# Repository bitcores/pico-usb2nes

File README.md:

# pico-usb2nes
RP2040 driven USB to controller interface for NES

This is based on the pico-usb2famikb project, using the same library for communicating with the NES/FC, but is focused on connecting to the controller port.

The only mode supported by default is the USB Keyboard Mouse Host mode (see [https://forums.nesdev.org/viewtopic.php?p=202489](https://forums.nesdev.org/viewtopic.php?p=202489) )

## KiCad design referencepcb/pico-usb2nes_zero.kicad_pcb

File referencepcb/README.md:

# pico-usb2nes Reference PCB
This directory contains reference a PCB design for the pico-usb2nes. It has not been designed by a experienced engineer, but it DOES work.

If you have some experience designing circuits like this, I would very much welcome improved designs.

For the reference design you will need:
* 1x Waveshare compatible RP2040-Zero
* 1x diode (I am using a 1N5819, 1N5817 better)
* 1x USB A type female port
* 2x 22ohm resistors
* 1x 100uf 16v capacitor (input from console)
* 1x four-channel logic level converter
* 1x NES controller port (PCB mountable)
* 5x pin headers (optional for i2c)

[This Youtube video](https://www.youtube.com/watch?v=ve_WcSxNZzQ) goes over the components and assembly.

These NES controller ports can be kinda hard to find, I will include a link to one source below (now unlisted, I am looking for other sources)

[https://aliexpress.com/item/1005009418780409.html](https://aliexpress.com/item/1005009418780409.html)

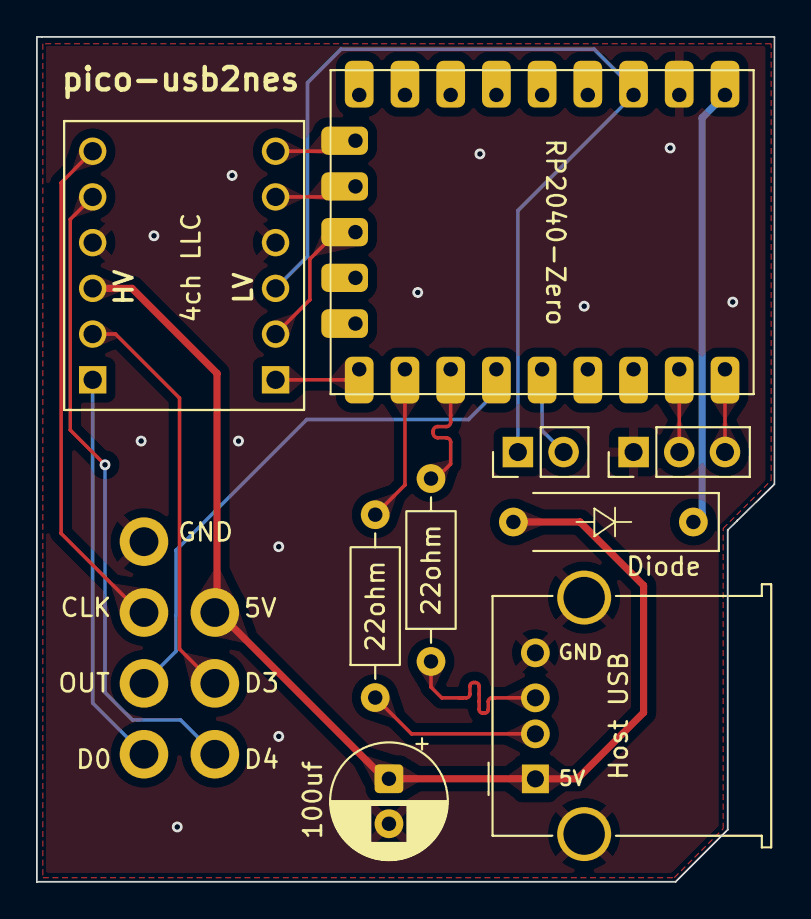
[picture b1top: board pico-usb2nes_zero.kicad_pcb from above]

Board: 2 copper layers, 41.0 x 46.9 mm, 8 parts (0 on the bottom side), 9 nets.

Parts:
4ch LLC: CONV_BOB-12009
22ohm, 22ohm#2: R_Axial_DIN0207_L6.3mm_D2.5mm_P10.16mm_Horizontal
100uf: CP_Radial_D6.3mm_P2.50mm
Diode: D_MELF-RM10_Universal_Handsoldering
Host USB: USB_A_Molex_67643_Horizontal
NES Controller Port: NES controller port
i2cENABLE: PinHeader_1x02_P2.54mm_Vertical

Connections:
5V: 4ch LLC.HV, 100uf.1, Diode.2, Host USB.1, NES Controller Port.5V
GND: 4ch LLC.GND_1, 4ch LLC.GND_2, 100uf.2, Host USB.4, Host USB.5, NES Controller Port.G
nesd0: 4ch LLC.HV1, NES Controller Port.D0
nesd3: 4ch LLC.HV2, NES Controller Port.D3
nesd4: 4ch LLC.HV3, NES Controller Port.D4
nesoe2: 4ch LLC.HV4, NES Controller Port.C
pico3.3v: 4ch LLC.LV, i2cENABLE.1
usb_d+: 22ohm.1, Host USB.3
usb_d-: 22ohm#2.1, Host USB.2

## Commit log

2025-10-19 initial release
2025-10-19 add pcb and gerbers
2025-11-02 docs updates
    added images and parts list, updated readme
2025-11-06 initial controller support
    take keyboard inputs as controller inputs
2025-12-16 Correct aliases for joypad keys
    Use the correct aliases for joypad keys and add a warning
2026-01-12 initial tasreplay support
    included is keyboard joypad support
2026-02-07 added initial gamepad support
    updated pio-usb library
    added initial gamepad support
2026-02-13 update i2c keyboard mouse handling
    fixed up how keyboard/mouse messages are handled via i2c
